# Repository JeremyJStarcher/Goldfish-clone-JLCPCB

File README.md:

# Goldfish-clone-JLCPCB

This board is a new layout for the original 
[Goldfish](https://github.com/staticintlucas/Goldfish)
by Lucas Jansen.

# REV A has several design issues that make it very difficult to attach the USB connector.

Do not use!

## Why?

This board was designed to be used with JLCPCB's SMD assembly service.  Because JLCPCB has very different requirements,
the board layout needed redesigned entirely.

## Important changes

* Four layer board with separate ground and power layers.  No additional charge, so why not?
* Board is wider to meet the minimum width requirements
* The board is longer to allow top-side labels all the way around
* Changed the USB connector to one that is more easily soldered by hand at the cost of making the board slightly thicker.
* Changed the crystal to match parts available.
* 0 Ohm resisters added to help USB data signal routing
* Additional USB Datapins removed.

## License Information
Released under the Creative Commons Attribution Share-Alike 4.0 License.  
https://creativecommons.org/licenses/by-sa/4.0/  

Original Arduino Mini Design by Team Arduino.  
Arduino Pro Mini Design by Spark Fun Electronics.  
Pro Micro Design by Spark Fun Electronics.  
Goldfish Design by Dr Derivative.  
JLCPCB assembly version by Jeremy J Starcher

## Revision History

* Rev A - Initial release.  On order - untested.

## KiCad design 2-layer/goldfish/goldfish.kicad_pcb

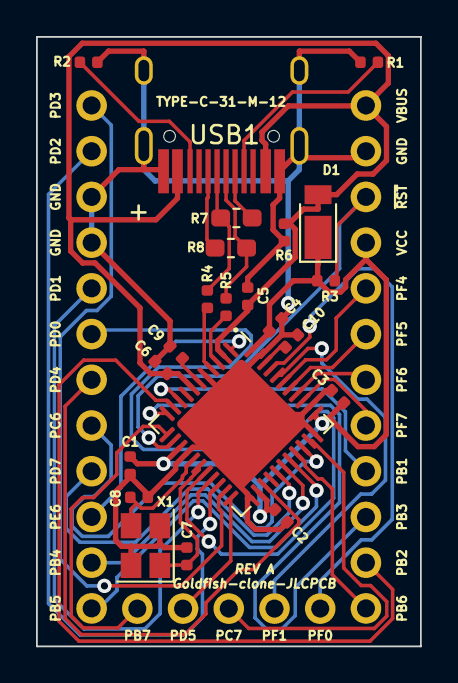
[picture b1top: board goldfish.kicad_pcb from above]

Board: 2 copper layers, 21.3 x 33.9 mm, 25 parts (0 on the bottom side), 39 nets.

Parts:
C1, C2, C3, C4, C5, C10: 0u1; C_0402_1005Metric
C6: 4u7; C_0402_1005Metric
C7, C8: 22p; C_0402_1005Metric
C9: 1u; C_0402_1005Metric
D1: D_Schottky; D_PowerDI-123
J3, J4: 01x12; Pins12
J5: 01x05; Pins5
R1, R2: 5k1; R_0402_1005Metric
R3, R6: 10k; R_0402_1005Metric
R4, R5: 22; R_0402_1005Metric
R7, R8: 0R; R_0603_1608Metric_Pad1.05x0.95mm_HandSolder
U1: ATmega32U4; QFN-44-1EP_7x7mm_P0.5mm_EP5.2x5.2mm
USB1: TYPE-C-31-M-12; HRO-TYPE-C-31-M-12-HandSoldering
X1: 16MHz; Crystal_SMD_SeikoEpson_TSX3225-4Pin_3.2x2.5mm

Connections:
/AREF: C10.1, U1.42
/D+: R4.2, R7.1, USB1.7
/D-: R5.2, R8.1, USB1.6
/PB1: J3.9, U1.9
/PB2: J3.11, U1.10
/PB3: J3.10, U1.11
/PB4: J4.2, U1.28
/PB5: J4.1, U1.29
/PB6: J3.12, U1.30
/PB7: J5.5, U1.12
/PC6: J4.5, U1.31
/PC7: J5.3, U1.32
/PD0: J4.7, U1.18
/PD1: J4.8, U1.19
/PD2: J4.11, U1.20
/PD3: J4.12, U1.21
/PD4: J4.6, U1.25
/PD5: J5.4, U1.22
/PD7: J4.4, U1.27
/PE6: J4.3, U1.1
/PF0: J5.1, U1.41
/PF1: J5.2, U1.40
/PF4: J3.5, U1.39
/PF5: J3.6, U1.38
/PF6: J3.7, U1.37
/PF7: J3.8, U1.36
/RESET: J3.3, R3.1, U1.13
/UCAP: C9.1, U1.6
GND: C1.2, C2.2, C3.2, C4.2, C5.2, C6.2, C7.2, C8.2, C9.2, C10.2, J3.2, J4.9, J4.10, R1.1, R2.1, R6.1, U1.5, U1.15, U1.23, U1.33, U1.35, U1.43, U1.45, USB1.1, USB1.12, USB1.13, X1.2, X1.4
unnamed: C7.1, U1.17, X1.1
unnamed: C8.1, U1.16, X1.3
unnamed: R1.2, USB1.4
unnamed: R2.2, USB1.10
unnamed: R4.1, U1.4
unnamed: R5.1, U1.3
unnamed: R7.2, USB1.5
unnamed: R8.2, USB1.8
VBUS: C5.1, C6.1, D1.2, J3.1, R6.2, U1.2, U1.7, USB1.2, USB1.11
VCC: C1.1, C2.1, C3.1, C4.1, D1.1, J3.4, R3.2, U1.14, U1.24, U1.34, U1.44

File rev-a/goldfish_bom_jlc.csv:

"Comment","Designator","Footprint","LCSC Part #"
"4u7","C6","C_0402_1005Metric","C23733"
"22p","C8,C7","C_0402_1005Metric","C1555"
"1u","C9","C_0402_1005Metric","C52923"
"0u1","C10,C1,C2,C3,C4,C5","C_0402_1005Metric","C1525"
"D_Schottky","D1","D_PowerDI-123","C8598"
"5k1","R2,R1","R_0402_1005Metric","C25905"
"10k","R3,R6","R_0402_1005Metric","C25744"
"22","R4,R5","R_0402_1005Metric","C25092"
"0R","R7,R8","R_0603_1608Metric_Pad1.05x0.95mm_HandSolder","C17168"
"ATmega32U4","U1","QFN-44-1EP_7x7mm_P0.5mm_EP5.2x5.2mm","C45874"
"16MHz","X1","Crystal_SMD_SeikoEpson_TSX3225-4Pin_3.2x2.5mm","C13738"

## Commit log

2020-11-26 Init commit
2020-11-29 Total board redesign
2020-11-30 Silk Screen layers cleaned up and labels added.
2020-11-30 Added README.md file
2020-11-30 Corrected typos and bad grammar
2020-12-01 Updated license and some documentation
2020-12-01 Added header pins to 3d model
2020-12-01 Added rendered pics
2020-12-03 Final version of REV A as submitted.
2020-12-03 Cleanup after submitting rev-a
2020-12-03 2Layer board - Rev A - not as comfortable with this.
2020-12-03 2Layer board - Rev A
2020-12-03 Updated .gitignore for new file layout
2020-12-15 Rev A updated. Don't use.
2020-12-15 Removed junk files
2021-04-12 Added the option for a USB-micro breakboard board on the USB as well.
